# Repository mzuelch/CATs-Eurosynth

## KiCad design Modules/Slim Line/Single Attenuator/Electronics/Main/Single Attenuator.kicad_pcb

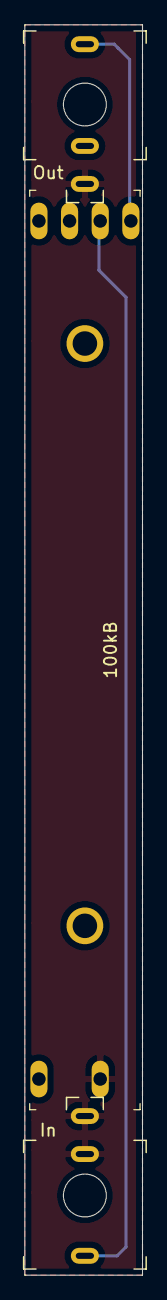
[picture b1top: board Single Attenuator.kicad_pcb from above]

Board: 2 copper layers, 9.6 x 102.0 mm, 3 parts (0 on the bottom side), 3 nets.

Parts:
J1: In; PJ-301-M-12
J2: Out; PJ-301-M-12
RV1: 100kB; Potentiometer_Fader_Alps_RS__01_Dual

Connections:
GND: J1.S, J1.TN, J2.S, RV1.3
unnamed: J1.T, RV1.1
unnamed: J2.T, RV1.2

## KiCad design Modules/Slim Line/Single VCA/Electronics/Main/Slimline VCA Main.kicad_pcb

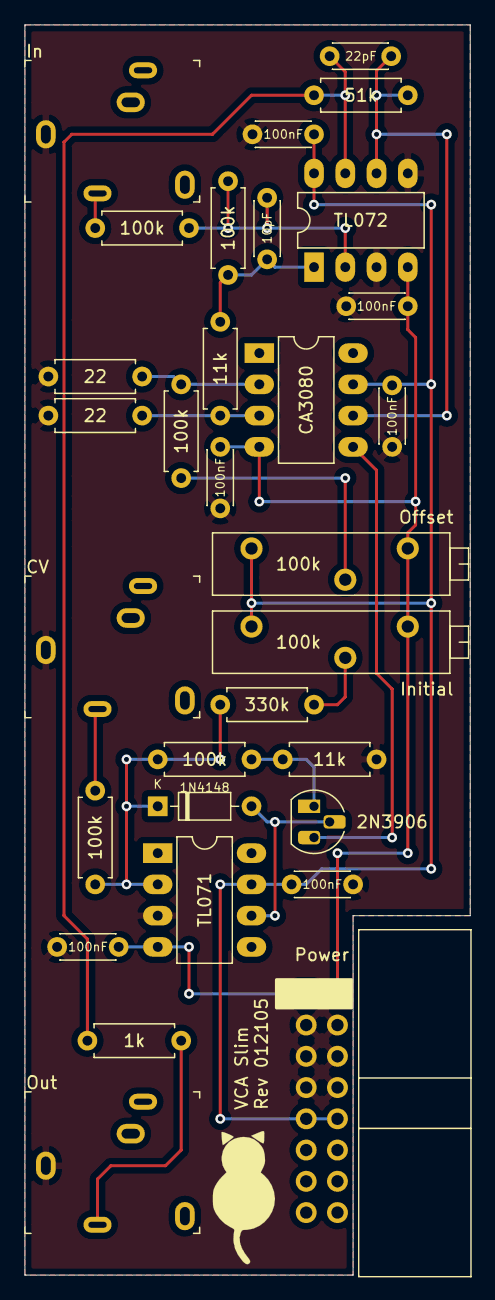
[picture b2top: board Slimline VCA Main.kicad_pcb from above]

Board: 2 copper layers, 36.2 x 101.6 mm, 31 parts (0 on the bottom side), 18 nets.

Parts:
C1: 10pF; C_Disc_D4.3mm_W1.9mm_P5.00mm
C2: 22pF; C_Disc_D4.3mm_W1.9mm_P5.00mm
C3, C4, C5, C6, C7, C8: 100nF; C_Disc_D4.3mm_W1.9mm_P5.00mm
D1: 1N4148; D_DO-35_SOD27_P7.62mm_Horizontal
J1: In; PJ-324M-3
J2: Out; PJ-324M-3
J3: CV; PJ-324M-3
J7: Power; IDC-Header_2x08_P2.54mm_Horizontal
Q1: 2N3906; TO-92_HandSolder
R1, R2, R7, R9, R12: 100k; R_Axial_DIN0207_L6.3mm_D2.5mm_P7.62mm_Horizontal
R3, R11: 11k; R_Axial_DIN0207_L6.3mm_D2.5mm_P7.62mm_Horizontal
R4, R8: 22; R_Axial_DIN0207_L6.3mm_D2.5mm_P7.62mm_Horizontal
R5: 51k; R_Axial_DIN0207_L6.3mm_D2.5mm_P7.62mm_Horizontal
R6: 1k; R_Axial_DIN0207_L6.3mm_D2.5mm_P7.62mm_Horizontal
R10: 330k; R_Axial_DIN0207_L6.3mm_D2.5mm_P7.62mm_Horizontal
RV1, RV2: 100k; Potentiometer_Bourns_3006P_Horizontal
U1: TL072; DIP-8_W7.62mm_LongPads
U2: CA3080; DIP-8_W7.62mm_LongPads
U3: TL071; DIP-8_W7.62mm_LongPads

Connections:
+12V: C3.2, C5.2, C6.2, J7.9, J7.10, RV1.1, RV2.1, U1.8, U2.7, U3.7
-12V: C4.1, C7.1, C8.1, J7.1, J7.2, RV1.3, RV2.3, U1.4, U2.4, U3.4
GND: C3.1, C4.2, C5.1, C6.1, C7.2, C8.2, J1.S, J2.S, J3.S, J7.3, J7.4, J7.5, J7.6, J7.7, J7.8, R4.1, R8.1, R11.2, U1.3, U1.5, U3.3
unnamed: C1.1, R2.1, R3.2, U1.1
unnamed: C1.2, R1.1, R2.2, U1.2
unnamed: C2.1, R5.1, R6.2, U1.7
unnamed: C2.2, R5.2, U1.6, U2.6
unnamed: D1.1, R9.1, R10.1, R12.1, U3.2
unnamed: D1.2, Q1.2, U3.6
unnamed: J1.T, R1.2
unnamed: J2.T, R6.1
unnamed: J3.T, R9.2
unnamed: Q1.1, R11.1, R12.2
unnamed: Q1.3, U2.5
unnamed: R3.1, R4.2, U2.3
unnamed: R7.1, R8.2, U2.2
unnamed: R7.2, RV1.2
unnamed: R10.2, RV2.2

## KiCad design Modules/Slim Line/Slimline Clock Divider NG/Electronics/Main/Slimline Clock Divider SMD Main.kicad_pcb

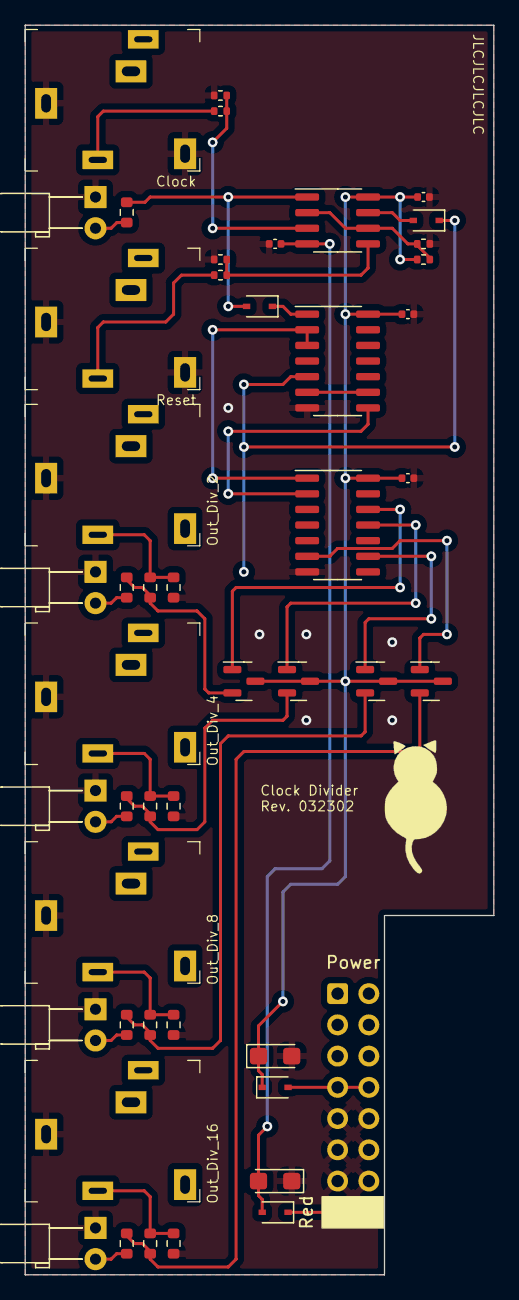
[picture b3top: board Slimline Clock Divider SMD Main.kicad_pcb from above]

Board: 2 copper layers, 38.1 x 101.6 mm, 48 parts (0 on the bottom side), 34 nets.

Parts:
C1, C4, C5, C6: 100nF; C_0402_1005Metric
C2, C3: 10uF/16V; CP_EIA-3216-18_Kemet-A
D1, D5, D6, D7, D8: LED; LED_D3.0mm_Horizontal_O3.81mm_Z6.0mm
D2, D4: 1N5819WS; D_SOD-323
D3, D9: 1N4148WS; D_SOD-323
IC1: TL072CDT; SOIC-8_3.9x4.9mm_P1.27mm
IC3: CD4069UBM96; SOIC-14_3.9x8.7mm_P1.27mm
IC4: CD4024BM96; SOIC-14_3.9x8.7mm_P1.27mm
J1: Clock; Jack_3.5mm_QingPu_WQP-PJ324M
J2: Out_Div_2; Jack_3.5mm_QingPu_WQP-PJ324M
J3: Out_Div_4; Jack_3.5mm_QingPu_WQP-PJ324M
J4: Reset; Jack_3.5mm_QingPu_WQP-PJ324M
J5: Out_Div_8; Jack_3.5mm_QingPu_WQP-PJ324M
J6: Out_Div_16; Jack_3.5mm_QingPu_WQP-PJ324M
J7: Power_2x5; Power_2x8_Horizontal
Q1, Q2, Q3, Q4: MMBT3904; SOT-23
R1, R2, R5: 100k; R_0402_1005Metric
R4, R10, R15: 10k; R_0402_1005Metric
R7, R14, R17, R19: 1k2; R_0603_1608Metric
R8, R12, R16, R18, R20, R21, R22, R23, R24: 1k; R_0603_1608Metric

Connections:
+12V: C1.1, C2.1, C4.1, C5.1, D2.1 (K), IC1.8 (V+), IC3.14 (VCC), IC4.14 (VCC), Q1.3 (C), Q2.3 (C), Q3.3 (C), Q4.3 (C), R1.2
-12V: C3.2, C6.2, D4.2 (A), IC1.4 (V-)
GND: C1.2, C2.2, C3.1, C4.2, C5.2, C6.1, D1.1 (K), D5.1 (K), D6.1 (K), D7.1 (K), D8.1 (K), IC3.7 (GND), IC4.7 (GND), J1.S, J1.TN, J2.S, J3.S, J4.S, J4.TN, J5.S, J6.S, J7.GND, R2.1, R5.1, R8.2, R15.1, R16.2, R18.2, R20.2
L/2: Q1.2 (E), R7.1, R21.1
L/4: Q2.2 (E), R14.1, R22.1
L/8: Q3.2 (E), R17.1, R23.1
L/16: Q4.2 (E), R19.1, R24.1
unnamed: D1.2 (A), R12.2
unnamed: D2.2 (A), J7.+12V
unnamed: D4.1 (K), J7.-12V
unnamed: D5.2 (A), R21.2
unnamed: D6.2 (A), R22.2
unnamed: D7.2 (A), R23.2
unnamed: D8.2 (A), R24.2
unnamed: D3.2 (A), IC1.1, R12.1
unnamed: IC1.2 (-), IC1.6 (-), R1.1, R15.2
unnamed: IC1.3 (+), R2.2, R4.2
unnamed: IC1.5 (+), R5.2, R10.2
unnamed: D9.2 (A), IC1.7
unnamed: D3.1 (K), IC3.1
unnamed: IC3.2, IC4.1 (~CP)
unnamed: D9.1 (K), IC3.5
unnamed: IC3.6, IC3.9
unnamed: IC3.8, IC4.2 (MR)
unnamed: IC4.6 (Q3), Q4.1 (B)
unnamed: IC4.9 (Q2), Q3.1 (B)
unnamed: IC4.11 (Q1), Q2.1 (B)
unnamed: IC4.12 (Q0), Q1.1 (B)
unnamed: J1.T, R4.1
unnamed: J2.T, R7.2, R8.1
unnamed: J3.T, R14.2, R16.1
unnamed: J4.T, R10.1
unnamed: J5.T, R17.2, R18.1
unnamed: J6.T, R19.2, R20.1
